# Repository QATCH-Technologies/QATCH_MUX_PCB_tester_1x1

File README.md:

# QATCH_MUX_PCB_tester_1x1
KiCad PCB model for testing SSRs to switch sensor signals (1x1)

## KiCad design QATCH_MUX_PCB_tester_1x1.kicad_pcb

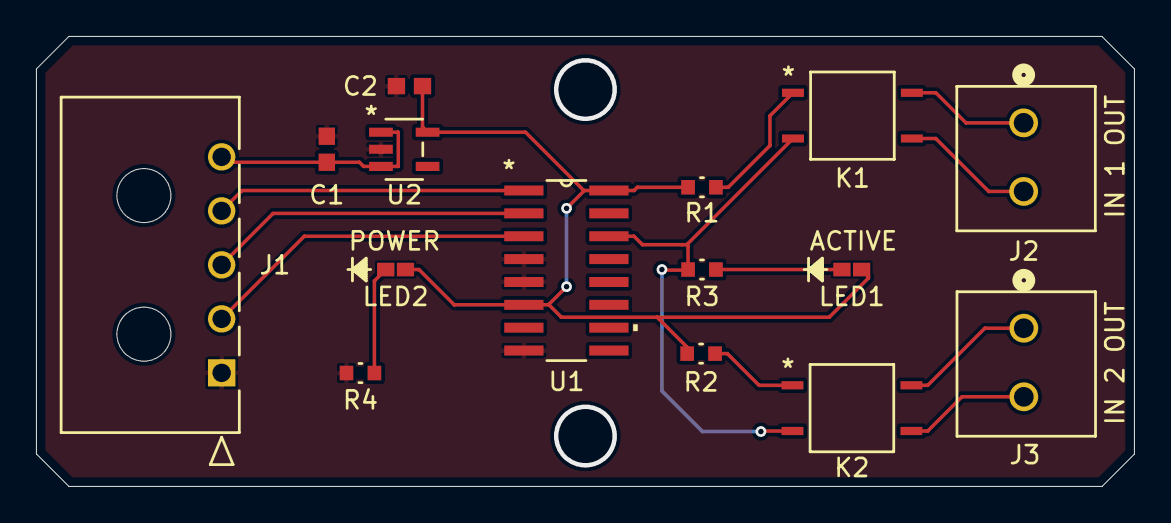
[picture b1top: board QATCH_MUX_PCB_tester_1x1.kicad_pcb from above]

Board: 2 copper layers, 61.0 x 25.0 mm, 15 parts (0 on the bottom side), 15 nets.

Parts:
C1, C2: 1uF; YAG_CC0603_YAG
J1: 436500500; CON_436500500_MOL
J2, J3: 1727010; CONN_1727010
K1, K2: C226S; C226S_COT
LED1, LED2: XZCM2CRK53WA-8VF; LED_SMD_XZCM_1P6X0P8_SLD
R1, R2: 470; RC0603N_YAG
R3, R4: 750; RC0603N_YAG
U1: CD74AC138M96; D16
U2: MIC5504; SOT-23-5_MC_MCH

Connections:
unnamed: J2.1, K1.4
unnamed: J2.2, K1.3
unnamed: J3.1, K2.4
unnamed: J3.2, K2.3
unnamed: K1.1, R1.2
unnamed: K2.1, R2.2
unnamed: LED1.1, R3.2
unnamed: LED2.1, R4.2
unnamed: C1.2, C2.1, J1.1, R4.1, U1.4 (*G2A), U1.5 (*G2B), U1.8 (GND), U2.2 (GND)
unnamed: J1.4, U1.1 (A)
unnamed: J1.3, U1.2 (B)
unnamed: J1.2, U1.3 (C)
unnamed: C2.2, LED1.2, LED2.2, R1.1, R2.1, U1.6 (G1), U1.16 (VCC), U2.5 (VOUT)
unnamed: K1.2, K2.2, R3.1, U1.14 (Y1)
unnamed: C1.1, J1.5, U2.1 (VIN), U2.3 (EN)

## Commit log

2024-05-16 Initial commit of KiCad project
2024-05-21 Add BOM and Pick and Place
2024-05-28 Add SVGs to project
2025-04-10 Committing local changes
